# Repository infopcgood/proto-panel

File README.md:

# proto-panel
LED panel PCB project compatible with Sigma Protogen by Coela Can't!

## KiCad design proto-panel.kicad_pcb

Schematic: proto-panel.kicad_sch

Parts:
D1, D2, D3, D4, D5, D6, D7, D8, D9, D10, D11, D12, D13, D14, D15, D16, D17, D18, D19, D20, D21, D22, D23, D24, D25, D26, D27, D28, D29, D30, D31, D32, D33, D34, D35, D36, D37, D38, D39, D40, D41, D42, D43, D44, D45, D46, D47, D48, D49, D50, D51, D52, D53, D54, D55, D56, D57, D58, D59, D60, D61, D62, D63, D64, D65, D66, D67, D68, D69, D70, D71, D72, D73, D74, D75, D76, D77, D78, D79, D80, D81, D82, D83, D84, D85, D86, D87, D88, D89, D90, D91, D92, D93, D94, D95, D96, D97, D98, D99, D100, D101, D102, D103, D104, D105, D106, D107, D108, D109, D110, D111, D112, D113, D114, D115, D116, D117, D118, D119, D120, D121, D122, D123, D124, D125, D126, D127, D128, D129, D130, D131, D132, D133, D134, D135, D136, D137, D138, D139, D140, D141, D142, D143, D144, D145, D146, D147, D148, D149, D150, D151, D152, D153, D154, D155, D156, D157, D158, D159, D160, D161, D162, D163, D164, D165, D166, D167, D168, D169, D170, D171, D172, D173, D174, D175, D176, D177, D178, D179, D180, D181, D182, D183, D184, D185, D186, D187, D188, D189, D190, D191, D192, D193, D194, D195, D196, D197, D198, D199, D200, D201, D202, D203, D204, D205, D206, D207, D208, D209, D210, D211, D212, D213, D214, D215, D216, D217, D218, D219, D220, D221, D222, D223, D224, D225, D226, D227, D228, D229, D230, D231, D232, D233, D234, D235, D236, D237, D238, D239, D240, D241, D242, D243, D244, D245, D246, D247, D248, D249, D250, D251, D252, D253, D254, D255, D256, D257, D258, D259, D260, D261, D262, D263, D264, D265, D266, D267, D268, D269, D270, D271, D272, D273, D274, D275, D276, D277, D278, D279, D280, D281, D282, D283, D284, D285, D286, D287, D288, D289, D290, D291, D292, D293, D294, D295, D296, D297, D298, D299, D300, D301, D302, D303, D304, D305, D306, D307, D308, D309, D310, D311, D312, D313, D314, D315, D316, D317, D318, D319, D320, D321, D322, D323, D324, D325, D326, D327, D328, D329, D330, D331, D332, D333, D334, D335, D336, D337, D338, D339, D340, D341, D342, D343, D344, D345, D346, D347, D348, D349, D350, D351, D352, D353, D354, D355, D356, D357, D358, D359, D360, D361, D362, D363, D364, D365, D366, D367, D368, D369, D370, D371, D372, D373, D374, D375, D376, D377, D378, D379, D380, D381, D382, D383, D384, D385, D386, D387, D388, D389, D390, D391, D392, D393, D394, D395, D396, D397, D398, D399, D400, D401, D402, D403, D404, D405, D406, D407, D408, D409, D410, D411, D412, D413, D414, D415, D416, D417, D418, D419, D420, D421, D422, D423, D424, D425, D426, D427, D428, D429, D430, D431, D432, D433, D434, D435, D436, D437, D438, D439, D440, D441, D442, D443, D444, D445, D446, D447, D448, D449, D450, D451, D452, D453, D454, D455, D456, D457, D458, D459, D460, D461, D462, D463, D464, D465, D466, D467, D468, D469, D470, D471, D472, D473, D474, D475, D476, D477, D478, D479, D480, D481, D482, D483, D484, D485, D486, D487, D488, D489, D490, D491, D492, D493, D494, D495, D496, D497, D498, D499, D500, D501, D502, D503, D504, D505, D506, D507, D508, D509, D510, D511, D512, D513, D514, D515, D516, D517, D518, D519, D520, D521, D522, D523, D524, D525, D526, D527, D528, D529, D530, D531, D532, D533, D534, D535, D536, D537, D538, D539, D540, D541, D542, D543, D544, D545, D546, D547, D548, D549, D550, D551, D552, D553, D554, D555, D556, D557, D558, D559, D560, D561, D562, D563, D564, D565, D566, D567, D568, D569, D570, D571, D572, D573, D574, D575, D576, D577, D578, D579, D580, D581, D582, D583, D584, D585, D586, D587, D588, D589, D590, D591, D592, D593, D594, D595, D596, D597, D598, D599, D600, D601, D602, D603, D604, D605, D606, D607, D608, D609, D610, D611, D612, D613, D614, D615, D616, D617, D618, D619, D620, D621, D622, D623, D624, D625, D626, D627, D628, D629, D630, D631, D632, D633, D634, D635, D636, D637, D638, D639, D640, D641, D642, D643, D644, D645, D646, D647, D648, D649, D650, D651, D652, D653, D654, D655, D656, D657, D658, D659, D660, D661, D662, D663, D664, D665, D666, D667, D668, D669, D670, D671, D672, D673, D674, D675, D676, D677, D678, D679, D680, D681, D682, D683, D684, D685, D686, D687, D688, D689, D690, D691, D692, D693, D694, D695, D696, D697, D698, D699, D700, D701, D702, D703, D704, D705, D706, D707, D708, D709, D710, D711, D712, D713, D714, D715, D716, D717, D718, D719, D720, D721, D722, D723, D724, D725, D726, D727, D728, D729, D730, D731, D733, D734, D735, D736, D737, D738, D739, D740, D741, D742, D743, D744, D745, D746, D747, D748, D749, D750, D751, D752, D753, D754, D755, D756, D757, D758, D759, D760, D761, D762, D763, D764, D765, D766, D767, D768, D769, D770, D771, D772, D773, D774, D775, D776, D778, D779, D780, D781, D782, D783, D784, D785, D786, D787, D788, D789, D790, D791, D792, D793, D794, D795, D796, D797, D798, D799, D800, D801, D802, D803, D804, D805, D806, D807, D808, D809, D810, D811, D812, D813, D814, D815, D816, D817, D818, D819, D820, D822, D823, D824, D825, D826, D827, D828, D829, D830, D831, D832, D833, D834, D835, D836, D837, D838, D839, D840, D841, D842, D843, D844, D845, D846, D847, D848, D849, D850, D851, D852, D853, D854, D855, D856, D857, D858, D859, D860, D861, D862, D864, D865, D866, D867, D868, D869, D870, D871, D872, D873, D874, D875, D876, D877, D878, D879, D880, D881, D882, D883, D884, D885, D886, D887, D888, D889, D890, D891, D892, D893, D894, D895, D896, D897, D898, D899, D900, D901, D902, D903, D904, D905, D906, D907, D908, D909, D910, D911, D912, D913, D914, D915, D916, D917, D918, D919, D920, D921, D922, D923, D924, D925, D926, D927, D928, D929, D930, D931, D932, D933, D934, D935, D936, D937, D938, D939, D940, D941, D942, D943, D944, D945, D946, D947, D948, D949, D950, D951, D952, D953, D954, D955, D956, D957, D958, D959, D960, D961, D962, D963, D964, D965, D966, D967, D968, D969, D970, D971, D972, D973, D974, D975, D976, D977, D978, D979, D980, D981, D982, D983, D984, D985, D986, D987, D988, D989, D990, D991, D992, D993, D994, D995, D996, D997, D998, D999, D1000, D1001, D1002, D1003, D1004, D1005, D1006, D1007, D1008, D1009, D1010, D1011, D1012, D1013, D1014, D1015, D1016, D1017, D1018, D1019, D1020, D1021, D1022, D1023, D1024, D1025, D1026, D1027, D1028, D1029, D1030, D1031, D1032, D1033, D1034, D1035, D1036, D1037, D1038, D1039, D1040, D1041, D1042, D1043, D1044, D1045, D1046, D1047, D1048, D1049, D1050, D1051, D1052, D1053, D1054, D1055, D1056, D1057, D1058, D1059, D1060, D1061, D1062, D1063, D1064, D1065, D1066, D1067, D1068, D1069, D1070, D1071, D1072, D1073, D1074, D1075, D1076, D1077, D1078, D1079, D1080, D1081, D1082, D1083, D1084, D1085, D1086, D1087, D1088, D1089, D1090, D1091, D1092, D1093, D1094, D1095, D1096, D1097, D1098, D1099, D1100, D1101, D1102, D1103, D1104, D1105, D1106, D1107, D1108, D1109, D1110, D1111, D1112, D1113, D1114, D1115, D1116, D1117, D1118, D1119, D1120, D1121, D1122, D1123, D1124, D1125, D1126, D1127, D1128, D1129, D1130, D1131, D1132, D1133, D1134, D1135, D1136, D1137, D1138, D1139, D1140, D1141, D1142, D1143, D1144, D1145, D1146, D1147, D1148, D1149, D1150, D1151, D1152, D1153, D1154, D1155, D1156, D1157, D1158, D1159, D1160, D1161, D1162, D1163, D1164, D1165, D1166, D1167, D1168, D1169, D1170, D1171, D1172, D1173, D1174, D1175, D1176, D1177, D1178, D1179, D1180, D1181, D1182, D1183, D1184, D1185, D1186, D1187, D1188, D1189, D1190, D1191, D1192, D1193, D1194, D1195, D1196, D1197, D1198, D1199, D1200: LED; LED_WS2812B-2020_PLCC4_2.0x2.0mm-VIAPADS; LCSC C965555
D732, D777, D821, D863: LED; LED_WS2812B-2020_PLCC4_2.0x2.0mm-VIAPADS
H1, H2, H3, H4, H5, H6, H7, H8, H9: MountingHole; MountingHole_2.2mm_M2
H10, H11: MountingHole_Pad; MountingHole_2.2mm_M2_Pad
J3: Conn_01x08_Socket; Hirose_FH12-8S-0.5SH_1x08-1MP_P0.50mm_Horizontal

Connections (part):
+5V: D1.4 (VDD), D2.4 (VDD), D3.4 (VDD), D4.4 (VDD), D5.4 (VDD), D6.4 (VDD), D7.4 (VDD), D8.4 (VDD), D9.4 (VDD), D10.4 (VDD), D11.4 (VDD), D12.4 (VDD), D13.4 (VDD), D14.4 (VDD), D15.4 (VDD), D16.4 (VDD), D17.4 (VDD), D18.4 (VDD), D19.4 (VDD), D20.4 (VDD), D21.4 (VDD), D22.4 (VDD), D23.4 (VDD), D24.4 (VDD), D25.4 (VDD), D26.4 (VDD), D27.4 (VDD), D28.4 (VDD), D29.4 (VDD), D30.4 (VDD), D31.4 (VDD), D32.4 (VDD), D33.4 (VDD), D34.4 (VDD), D35.4 (VDD), D36.4 (VDD), D37.4 (VDD), D38.4 (VDD), D39.4 (VDD), D40.4 (VDD), D41.4 (VDD), D42.4 (VDD), D43.4 (VDD), D44.4 (VDD), D45.4 (VDD), D46.4 (VDD), D47.4 (VDD), D48.4 (VDD), D49.4 (VDD), D50.4 (VDD), D51.4 (VDD), D52.4 (VDD), D53.4 (VDD), D54.4 (VDD), D55.4 (VDD), D56.4 (VDD), D57.4 (VDD), D58.4 (VDD), D59.4 (VDD), D60.4 (VDD), D61.4 (VDD), D62.4 (VDD), D63.4 (VDD), D64.4 (VDD), D65.4 (VDD), D66.4 (VDD), D67.4 (VDD), D68.4 (VDD), D69.4 (VDD), D70.4 (VDD), D71.4 (VDD), D72.4 (VDD), D73.4 (VDD), D74.4 (VDD), D75.4 (VDD), D76.4 (VDD), D77.4 (VDD), D78.4 (VDD), D79.4 (VDD), D80.4 (VDD)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
GND: D1.2 (VSS), D2.2 (VSS), D3.2 (VSS), D4.2 (VSS), D5.2 (VSS), D6.2 (VSS), D7.2 (VSS), D8.2 (VSS), D9.2 (VSS), D10.2 (VSS), D11.2 (VSS), D12.2 (VSS), D13.2 (VSS), D14.2 (VSS), D15.2 (VSS), D16.2 (VSS), D17.2 (VSS), D18.2 (VSS), D19.2 (VSS), D20.2 (VSS), D21.2 (VSS), D22.2 (VSS), D23.2 (VSS), D24.2 (VSS), D25.2 (VSS), D26.2 (VSS), D27.2 (VSS), D28.2 (VSS), D29.2 (VSS), D30.2 (VSS), D31.2 (VSS), D32.2 (VSS), D33.2 (VSS), D34.2 (VSS), D35.2 (VSS), D36.2 (VSS), D37.2 (VSS), D38.2 (VSS), D39.2 (VSS), D40.2 (VSS), D41.2 (VSS), D42.2 (VSS), D43.2 (VSS), D44.2 (VSS), D45.2 (VSS), D46.2 (VSS), D47.2 (VSS), D48.2 (VSS), D49.2 (VSS), D50.2 (VSS), D51.2 (VSS), D52.2 (VSS), D53.2 (VSS), D54.2 (VSS), D55.2 (VSS), D56.2 (VSS), D57.2 (VSS), D58.2 (VSS), D59.2 (VSS), D60.2 (VSS), D61.2 (VSS), D62.2 (VSS), D63.2 (VSS), D64.2 (VSS), D65.2 (VSS), D66.2 (VSS), D67.2 (VSS), D68.2 (VSS), D69.2 (VSS), D70.2 (VSS), D71.2 (VSS), D72.2 (VSS), D73.2 (VSS), D74.2 (VSS), D75.2 (VSS), D76.2 (VSS), D77.2 (VSS), D78.2 (VSS), D79.2 (VSS), D80.2 (VSS)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
unnamed: D1.1 (DOUT), D2.3 (DIN)
unnamed: D2.1 (DOUT), D3.3 (DIN)
unnamed: D3.1 (DOUT), D4.3 (DIN)
unnamed: D4.1 (DOUT), D5.3 (DIN)
unnamed: D5.1 (DOUT), D6.3 (DIN)
unnamed: D6.1 (DOUT), D7.3 (DIN)
unnamed: D7.1 (DOUT), D8.3 (DIN)
unnamed: D8.1 (DOUT), D9.3 (DIN)
unnamed: D9.1 (DOUT), D10.3 (DIN)
unnamed: D10.1 (DOUT), D11.3 (DIN)
unnamed: D11.1 (DOUT), D12.3 (DIN)
unnamed: D12.1 (DOUT), D13.3 (DIN)
unnamed: D13.1 (DOUT), D14.3 (DIN)
unnamed: D14.1 (DOUT), D15.3 (DIN)
unnamed: D15.1 (DOUT), D16.3 (DIN)
unnamed: D16.1 (DOUT), D17.3 (DIN)
unnamed: D17.1 (DOUT), D18.3 (DIN)
unnamed: D18.1 (DOUT), D19.3 (DIN)
unnamed: D19.1 (DOUT), D20.3 (DIN)
unnamed: D20.1 (DOUT), D21.3 (DIN)
unnamed: D21.1 (DOUT), D22.3 (DIN)
unnamed: D22.1 (DOUT), D23.3 (DIN)
unnamed: D23.1 (DOUT), D24.3 (DIN)
unnamed: D24.1 (DOUT), D25.3 (DIN)
unnamed: D25.1 (DOUT), D26.3 (DIN)
unnamed: D26.1 (DOUT), D27.3 (DIN)
unnamed: D27.1 (DOUT), D28.3 (DIN)
unnamed: D28.1 (DOUT), D29.3 (DIN)
unnamed: D29.1 (DOUT), D30.3 (DIN)
unnamed: D30.1 (DOUT), D31.3 (DIN)
unnamed: D31.1 (DOUT), D32.3 (DIN)
unnamed: D32.1 (DOUT), D33.3 (DIN)
unnamed: D33.1 (DOUT), D34.3 (DIN)
unnamed: D34.1 (DOUT), D35.3 (DIN)
unnamed: D35.1 (DOUT), D36.3 (DIN)
unnamed: D36.1 (DOUT), D37.3 (DIN)
unnamed: D37.1 (DOUT), D38.3 (DIN)
unnamed: D38.1 (DOUT), D39.3 (DIN)
unnamed: D39.1 (DOUT), D40.3 (DIN)
unnamed: D40.1 (DOUT), D41.3 (DIN)
unnamed: D41.1 (DOUT), D42.3 (DIN)
unnamed: D42.1 (DOUT), D43.3 (DIN)
unnamed: D43.1 (DOUT), D44.3 (DIN)
unnamed: D44.1 (DOUT), D45.3 (DIN)
unnamed: D45.1 (DOUT), D46.3 (DIN)
unnamed: D46.1 (DOUT), D47.3 (DIN)
unnamed: D47.1 (DOUT), D48.3 (DIN)
unnamed: D48.1 (DOUT), D49.3 (DIN)
unnamed: D49.1 (DOUT), D50.3 (DIN)
unnamed: D50.1 (DOUT), D51.3 (DIN)
unnamed: D51.1 (DOUT), D52.3 (DIN)
unnamed: D52.1 (DOUT), D53.3 (DIN)
unnamed: D53.1 (DOUT), D54.3 (DIN)
unnamed: D54.1 (DOUT), D55.3 (DIN)
unnamed: D55.1 (DOUT), D56.3 (DIN)
unnamed: D56.1 (DOUT), D57.3 (DIN)
unnamed: D57.1 (DOUT), D58.3 (DIN)
unnamed: D58.1 (DOUT), D59.3 (DIN)
unnamed: D59.1 (DOUT), D60.3 (DIN)
unnamed: D60.1 (DOUT), D61.3 (DIN)
unnamed: D61.1 (DOUT), D62.3 (DIN)
unnamed: D62.1 (DOUT), D63.3 (DIN)
unnamed: D63.1 (DOUT), D64.3 (DIN)
unnamed: D64.1 (DOUT), D65.3 (DIN)
unnamed: D65.1 (DOUT), D66.3 (DIN)
unnamed: D66.1 (DOUT), D67.3 (DIN)
unnamed: D67.1 (DOUT), D68.3 (DIN)
unnamed: D68.1 (DOUT), D69.3 (DIN)
unnamed: D69.1 (DOUT), D70.3 (DIN)
unnamed: D70.1 (DOUT), D71.3 (DIN)
unnamed: D71.1 (DOUT), D72.3 (DIN)
unnamed: D72.1 (DOUT), D73.3 (DIN)
unnamed: D73.1 (DOUT), D74.3 (DIN)
unnamed: D74.1 (DOUT), D75.3 (DIN)
unnamed: D75.1 (DOUT), D76.3 (DIN)
unnamed: D76.1 (DOUT), D77.3 (DIN)
unnamed: D77.1 (DOUT), D78.3 (DIN)
unnamed: D78.1 (DOUT), D79.3 (DIN)
unnamed: D79.1 (DOUT), D80.3 (DIN)
unnamed: D80.1 (DOUT), D81.3 (DIN)
unnamed: D81.1 (DOUT), D82.3 (DIN)
unnamed: D82.1 (DOUT), D83.3 (DIN)
unnamed: D83.1 (DOUT), D84.3 (DIN)
unnamed: D84.1 (DOUT), D85.3 (DIN)
unnamed: D85.1 (DOUT), D86.3 (DIN)
unnamed: D86.1 (DOUT), D87.3 (DIN)
unnamed: D87.1 (DOUT), D88.3 (DIN)
unnamed: D88.1 (DOUT), D89.3 (DIN)
unnamed: D89.1 (DOUT), D90.3 (DIN)
unnamed: D90.1 (DOUT), D91.3 (DIN)
unnamed: D91.1 (DOUT), D92.3 (DIN)
unnamed: D92.1 (DOUT), D93.3 (DIN)
unnamed: D93.1 (DOUT), D94.3 (DIN)
unnamed: D94.1 (DOUT), D95.3 (DIN)
unnamed: D95.1 (DOUT), D96.3 (DIN)
unnamed: D96.1 (DOUT), D97.3 (DIN)
unnamed: D97.1 (DOUT), D98.3 (DIN)
unnamed: D98.1 (DOUT), D99.3 (DIN)
unnamed: D99.1 (DOUT), D100.3 (DIN)
unnamed: D100.1 (DOUT), D101.3 (DIN)
unnamed: D101.1 (DOUT), D102.3 (DIN)
unnamed: D102.1 (DOUT), D103.3 (DIN)
unnamed: D103.1 (DOUT), D104.3 (DIN)
unnamed: D104.1 (DOUT), D105.3 (DIN)
unnamed: D105.1 (DOUT), D106.3 (DIN)
unnamed: D106.1 (DOUT), D107.3 (DIN)
unnamed: D107.1 (DOUT), D108.3 (DIN)
unnamed: D108.1 (DOUT), D109.3 (DIN)
unnamed: D109.1 (DOUT), D110.3 (DIN)
unnamed: D110.1 (DOUT), D111.3 (DIN)
unnamed: D111.1 (DOUT), D112.3 (DIN)
unnamed: D112.1 (DOUT), D113.3 (DIN)
unnamed: D113.1 (DOUT), D114.3 (DIN)
unnamed: D114.1 (DOUT), D115.3 (DIN)
unnamed: D115.1 (DOUT), D116.3 (DIN)
unnamed: D116.1 (DOUT), D117.3 (DIN)
unnamed: D117.1 (DOUT), D118.3 (DIN)
unnamed: D118.1 (DOUT), D119.3 (DIN)
unnamed: D119.1 (DOUT), D120.3 (DIN)
unnamed: D120.1 (DOUT), D121.3 (DIN)
unnamed: D121.1 (DOUT), D122.3 (DIN)
unnamed: D122.1 (DOUT), D123.3 (DIN)
unnamed: D123.1 (DOUT), D124.3 (DIN)
unnamed: D124.1 (DOUT), D125.3 (DIN)
unnamed: D125.1 (DOUT), D126.3 (DIN)
unnamed: D126.1 (DOUT), D127.3 (DIN)
unnamed: D127.1 (DOUT), D128.3 (DIN)
unnamed: D128.1 (DOUT), D129.3 (DIN)
unnamed: D129.1 (DOUT), D130.3 (DIN)
unnamed: D130.1 (DOUT), D131.3 (DIN)
unnamed: D131.1 (DOUT), D132.3 (DIN)
unnamed: D132.1 (DOUT), D133.3 (DIN)
unnamed: D133.1 (DOUT), D134.3 (DIN)
unnamed: D134.1 (DOUT), D135.3 (DIN)
unnamed: D135.1 (DOUT), D136.3 (DIN)
unnamed: D136.1 (DOUT), D137.3 (DIN)
unnamed: D137.1 (DOUT), D138.3 (DIN)
unnamed: D138.1 (DOUT), D139.3 (DIN)
unnamed: D139.1 (DOUT), D140.3 (DIN)
unnamed: D140.1 (DOUT), D141.3 (DIN)
unnamed: D141.1 (DOUT), D142.3 (DIN)
unnamed: D142.1 (DOUT), D143.3 (DIN)
unnamed: D143.1 (DOUT), D144.3 (DIN)
unnamed: D144.1 (DOUT), D145.3 (DIN)
unnamed: D145.1 (DOUT), D146.3 (DIN)
unnamed: D146.1 (DOUT), D147.3 (DIN)
unnamed: D147.1 (DOUT), D148.3 (DIN)
unnamed: D148.1 (DOUT), D149.3 (DIN)
unnamed: D149.1 (DOUT), D150.3 (DIN)
unnamed: D151.1 (DOUT), D152.3 (DIN)
unnamed: D152.1 (DOUT), D153.3 (DIN)
unnamed: D153.1 (DOUT), D154.3 (DIN)
unnamed: D154.1 (DOUT), D155.3 (DIN)
unnamed: D155.1 (DOUT), D156.3 (DIN)
unnamed: D156.1 (DOUT), D157.3 (DIN)
unnamed: D157.1 (DOUT), D158.3 (DIN)
unnamed: D158.1 (DOUT), D159.3 (DIN)
unnamed: D159.1 (DOUT), D160.3 (DIN)
unnamed: D160.1 (DOUT), D161.3 (DIN)
unnamed: D161.1 (DOUT), D162.3 (DIN)
unnamed: D162.1 (DOUT), D163.3 (DIN)
unnamed: D163.1 (DOUT), D164.3 (DIN)
unnamed: D164.1 (DOUT), D165.3 (DIN)
unnamed: D165.1 (DOUT), D166.3 (DIN)
unnamed: D166.1 (DOUT), D167.3 (DIN)
unnamed: D167.1 (DOUT), D168.3 (DIN)
unnamed: D168.1 (DOUT), D169.3 (DIN)
unnamed: D169.1 (DOUT), D170.3 (DIN)
unnamed: D170.1 (DOUT), D171.3 (DIN)
unnamed: D171.1 (DOUT), D172.3 (DIN)
unnamed: D172.1 (DOUT), D173.3 (DIN)
unnamed: D173.1 (DOUT), D174.3 (DIN)
unnamed: D174.1 (DOUT), D175.3 (DIN)
unnamed: D175.1 (DOUT), D176.3 (DIN)
unnamed: D176.1 (DOUT), D177.3 (DIN)
unnamed: D177.1 (DOUT), D178.3 (DIN)
unnamed: D178.1 (DOUT), D179.3 (DIN)
unnamed: D179.1 (DOUT), D180.3 (DIN)
unnamed: D180.1 (DOUT), D181.3 (DIN)
unnamed: D181.1 (DOUT), D182.3 (DIN)
unnamed: D182.1 (DOUT), D183.3 (DIN)
unnamed: D183.1 (DOUT), D184.3 (DIN)
unnamed: D184.1 (DOUT), D185.3 (DIN)
unnamed: D185.1 (DOUT), D186.3 (DIN)
unnamed: D186.1 (DOUT), D187.3 (DIN)
unnamed: D187.1 (DOUT), D188.3 (DIN)
unnamed: D188.1 (DOUT), D189.3 (DIN)
unnamed: D189.1 (DOUT), D190.3 (DIN)
unnamed: D190.1 (DOUT), D191.3 (DIN)
unnamed: D191.1 (DOUT), D192.3 (DIN)
unnamed: D192.1 (DOUT), D193.3 (DIN)
unnamed: D193.1 (DOUT), D194.3 (DIN)
unnamed: D194.1 (DOUT), D195.3 (DIN)
unnamed: D195.1 (DOUT), D196.3 (DIN)
unnamed: D196.1 (DOUT), D197.3 (DIN)
unnamed: D197.1 (DOUT), D198.3 (DIN)
unnamed: D198.1 (DOUT), D199.3 (DIN)
unnamed: D199.1 (DOUT), D200.3 (DIN)
unnamed: D200.1 (DOUT), D201.3 (DIN)
unnamed: D201.1 (DOUT), D202.3 (DIN)
unnamed: D202.1 (DOUT), D203.3 (DIN)
unnamed: D203.1 (DOUT), D204.3 (DIN)
unnamed: D204.1 (DOUT), D205.3 (DIN)
unnamed: D205.1 (DOUT), D206.3 (DIN)
unnamed: D206.1 (DOUT), D207.3 (DIN)
unnamed: D207.1 (DOUT), D208.3 (DIN)
unnamed: D208.1 (DOUT), D209.3 (DIN)
unnamed: D209.1 (DOUT), D210.3 (DIN)
unnamed: D210.1 (DOUT), D211.3 (DIN)
unnamed: D211.1 (DOUT), D212.3 (DIN)
unnamed: D212.1 (DOUT), D213.3 (DIN)
unnamed: D213.1 (DOUT), D214.3 (DIN)
unnamed: D214.1 (DOUT), D215.3 (DIN)
unnamed: D215.1 (DOUT), D216.3 (DIN)
unnamed: D216.1 (DOUT), D217.3 (DIN)
unnamed: D217.1 (DOUT), D218.3 (DIN)
unnamed: D218.1 (DOUT), D219.3 (DIN)
unnamed: D219.1 (DOUT), D220.3 (DIN)
unnamed: D220.1 (DOUT), D221.3 (DIN)
unnamed: D221.1 (DOUT), D222.3 (DIN)
unnamed: D222.1 (DOUT), D223.3 (DIN)
unnamed: D223.1 (DOUT), D224.3 (DIN)
unnamed: D224.1 (DOUT), D225.3 (DIN)
unnamed: D225.1 (DOUT), D226.3 (DIN)
unnamed: D226.1 (DOUT), D227.3 (DIN)
unnamed: D227.1 (DOUT), D228.3 (DIN)
unnamed: D228.1 (DOUT), D229.3 (DIN)
unnamed: D229.1 (DOUT), D230.3 (DIN)
unnamed: D230.1 (DOUT), D231.3 (DIN)
unnamed: D231.1 (DOUT), D232.3 (DIN)
unnamed: D232.1 (DOUT), D233.3 (DIN)
unnamed: D233.1 (DOUT), D234.3 (DIN)
unnamed: D234.1 (DOUT), D235.3 (DIN)
unnamed: D235.1 (DOUT), D236.3 (DIN)
unnamed: D236.1 (DOUT), D237.3 (DIN)
unnamed: D237.1 (DOUT), D238.3 (DIN)
unnamed: D238.1 (DOUT), D239.3 (DIN)
unnamed: D239.1 (DOUT), D240.3 (DIN)
unnamed: D240.1 (DOUT), D241.3 (DIN)
unnamed: D241.1 (DOUT), D242.3 (DIN)
unnamed: D242.1 (DOUT), D243.3 (DIN)
unnamed: D243.1 (DOUT), D244.3 (DIN)
unnamed: D244.1 (DOUT), D245.3 (DIN)
unnamed: D245.1 (DOUT), D246.3 (DIN)
unnamed: D246.1 (DOUT), D247.3 (DIN)
unnamed: D247.1 (DOUT), D248.3 (DIN)
unnamed: D248.1 (DOUT), D249.3 (DIN)
unnamed: D249.1 (DOUT), D250.3 (DIN)
unnamed: D250.1 (DOUT), D251.3 (DIN)
unnamed: D251.1 (DOUT), D252.3 (DIN)
unnamed: D252.1 (DOUT), D253.3 (DIN)
unnamed: D253.1 (DOUT), D254.3 (DIN)
unnamed: D254.1 (DOUT), D255.3 (DIN)
unnamed: D255.1 (DOUT), D256.3 (DIN)
unnamed: D256.1 (DOUT), D257.3 (DIN)
unnamed: D257.1 (DOUT), D258.3 (DIN)
unnamed: D258.1 (DOUT), D259.3 (DIN)
unnamed: D259.1 (DOUT), D260.3 (DIN)
unnamed: D260.1 (DOUT), D261.3 (DIN)
unnamed: D261.1 (DOUT), D262.3 (DIN)
unnamed: D262.1 (DOUT), D263.3 (DIN)
unnamed: D263.1 (DOUT), D264.3 (DIN)
unnamed: D264.1 (DOUT), D265.3 (DIN)
unnamed: D265.1 (DOUT), D266.3 (DIN)
unnamed: D266.1 (DOUT), D267.3 (DIN)
unnamed: D267.1 (DOUT), D268.3 (DIN)
unnamed: D268.1 (DOUT), D269.3 (DIN)
unnamed: D269.1 (DOUT), D270.3 (DIN)
unnamed: D270.1 (DOUT), D271.3 (DIN)
unnamed: D271.1 (DOUT), D272.3 (DIN)
unnamed: D272.1 (DOUT), D273.3 (DIN)
unnamed: D273.1 (DOUT), D274.3 (DIN)
unnamed: D274.1 (DOUT), D275.3 (DIN)
unnamed: D275.1 (DOUT), D276.3 (DIN)
unnamed: D276.1 (DOUT), D277.3 (DIN)
unnamed: D277.1 (DOUT), D278.3 (DIN)
unnamed: D278.1 (DOUT), D279.3 (DIN)
unnamed: D279.1 (DOUT), D280.3 (DIN)
unnamed: D280.1 (DOUT), D281.3 (DIN)
unnamed: D281.1 (DOUT), D282.3 (DIN)
unnamed: D282.1 (DOUT), D283.3 (DIN)
unnamed: D283.1 (DOUT), D284.3 (DIN)
unnamed: D284.1 (DOUT), D285.3 (DIN)
unnamed: D285.1 (DOUT), D286.3 (DIN)
unnamed: D286.1 (DOUT), D287.3 (DIN)
unnamed: D287.1 (DOUT), D288.3 (DIN)
unnamed: D288.1 (DOUT), D289.3 (DIN)
unnamed: D289.1 (DOUT), D290.3 (DIN)
unnamed: D290.1 (DOUT), D291.3 (DIN)
unnamed: D291.1 (DOUT), D292.3 (DIN)
unnamed: D292.1 (DOUT), D293.3 (DIN)
unnamed: D293.1 (DOUT), D294.3 (DIN)
unnamed: D294.1 (DOUT), D295.3 (DIN)
unnamed: D295.1 (DOUT), D296.3 (DIN)
unnamed: D296.1 (DOUT), D297.3 (DIN)
unnamed: D297.1 (DOUT), D298.3 (DIN)
unnamed: D298.1 (DOUT), D299.3 (DIN)
unnamed: D299.1 (DOUT), D300.3 (DIN)
unnamed: D301.1 (DOUT), D302.3 (DIN)
unnamed: D302.1 (DOUT), D303.3 (DIN)
unnamed: D303.1 (DOUT), D304.3 (DIN)
unnamed: D304.1 (DOUT), D305.3 (DIN)
unnamed: D305.1 (DOUT), D306.3 (DIN)
unnamed: D306.1 (DOUT), D307.3 (DIN)
unnamed: D307.1 (DOUT), D308.3 (DIN)
unnamed: D308.1 (DOUT), D309.3 (DIN)
unnamed: D309.1 (DOUT), D310.3 (DIN)
unnamed: D310.1 (DOUT), D311.3 (DIN)
unnamed: D311.1 (DOUT), D312.3 (DIN)
unnamed: D312.1 (DOUT), D313.3 (DIN)
unnamed: D313.1 (DOUT), D314.3 (DIN)
unnamed: D314.1 (DOUT), D315.3 (DIN)
unnamed: D315.1 (DOUT), D316.3 (DIN)
unnamed: D316.1 (DOUT), D317.3 (DIN)
unnamed: D317.1 (DOUT), D318.3 (DIN)
unnamed: D318.1 (DOUT), D319.3 (DIN)
unnamed: D319.1 (DOUT), D320.3 (DIN)
unnamed: D320.1 (DOUT), D321.3 (DIN)
unnamed: D321.1 (DOUT), D322.3 (DIN)
unnamed: D322.1 (DOUT), D323.3 (DIN)
unnamed: D323.1 (DOUT), D324.3 (DIN)
unnamed: D324.1 (DOUT), D325.3 (DIN)
unnamed: D325.1 (DOUT), D326.3 (DIN)
unnamed: D326.1 (DOUT), D327.3 (DIN)
unnamed: D327.1 (DOUT), D328.3 (DIN)
unnamed: D328.1 (DOUT), D329.3 (DIN)
unnamed: D329.1 (DOUT), D330.3 (DIN)
unnamed: D330.1 (DOUT), D331.3 (DIN)
unnamed: D331.1 (DOUT), D332.3 (DIN)
unnamed: D332.1 (DOUT), D333.3 (DIN)
unnamed: D333.1 (DOUT), D334.3 (DIN)
unnamed: D334.1 (DOUT), D335.3 (DIN)
unnamed: D335.1 (DOUT), D336.3 (DIN)
unnamed: D336.1 (DOUT), D337.3 (DIN)
unnamed: D337.1 (DOUT), D338.3 (DIN)
unnamed: D338.1 (DOUT), D339.3 (DIN)
unnamed: D339.1 (DOUT), D340.3 (DIN)
unnamed: D340.1 (DOUT), D341.3 (DIN)
unnamed: D341.1 (DOUT), D342.3 (DIN)
unnamed: D342.1 (DOUT), D343.3 (DIN)
unnamed: D343.1 (DOUT), D344.3 (DIN)
unnamed: D344.1 (DOUT), D345.3 (DIN)
unnamed: D345.1 (DOUT), D346.3 (DIN)
unnamed: D346.1 (DOUT), D347.3 (DIN)
unnamed: D347.1 (DOUT), D348.3 (DIN)
unnamed: D348.1 (DOUT), D349.3 (DIN)
unnamed: D349.1 (DOUT), D350.3 (DIN)
unnamed: D350.1 (DOUT), D351.3 (DIN)
unnamed: D351.1 (DOUT), D352.3 (DIN)
unnamed: D352.1 (DOUT), D353.3 (DIN)
unnamed: D353.1 (DOUT), D354.3 (DIN)
unnamed: D354.1 (DOUT), D355.3 (DIN)
unnamed: D355.1 (DOUT), D356.3 (DIN)
unnamed: D356.1 (DOUT), D357.3 (DIN)
unnamed: D357.1 (DOUT), D358.3 (DIN)
unnamed: D358.1 (DOUT), D359.3 (DIN)
unnamed: D359.1 (DOUT), D360.3 (DIN)
unnamed: D360.1 (DOUT), D361.3 (DIN)
unnamed: D361.1 (DOUT), D362.3 (DIN)
unnamed: D362.1 (DOUT), D363.3 (DIN)
unnamed: D363.1 (DOUT), D364.3 (DIN)
unnamed: D364.1 (DOUT), D365.3 (DIN)
unnamed: D365.1 (DOUT), D366.3 (DIN)
unnamed: D366.1 (DOUT), D367.3 (DIN)
unnamed: D367.1 (DOUT), D368.3 (DIN)
unnamed: D368.1 (DOUT), D369.3 (DIN)
unnamed: D369.1 (DOUT), D370.3 (DIN)
unnamed: D370.1 (DOUT), D371.3 (DIN)
unnamed: D371.1 (DOUT), D372.3 (DIN)
unnamed: D372.1 (DOUT), D373.3 (DIN)
unnamed: D373.1 (DOUT), D374.3 (DIN)
unnamed: D374.1 (DOUT), D375.3 (DIN)
unnamed: D375.1 (DOUT), D376.3 (DIN)
unnamed: D376.1 (DOUT), D377.3 (DIN)
unnamed: D377.1 (DOUT), D378.3 (DIN)
unnamed: D378.1 (DOUT), D379.3 (DIN)
unnamed: D379.1 (DOUT), D380.3 (DIN)
unnamed: D380.1 (DOUT), D381.3 (DIN)
unnamed: D381.1 (DOUT), D382.3 (DIN)
unnamed: D382.1 (DOUT), D383.3 (DIN)
unnamed: D383.1 (DOUT), D384.3 (DIN)
unnamed: D384.1 (DOUT), D385.3 (DIN)
unnamed: D385.1 (DOUT), D386.3 (DIN)
unnamed: D386.1 (DOUT), D387.3 (DIN)
unnamed: D387.1 (DOUT), D388.3 (DIN)
unnamed: D388.1 (DOUT), D389.3 (DIN)
unnamed: D389.1 (DOUT), D390.3 (DIN)
unnamed: D390.1 (DOUT), D391.3 (DIN)
unnamed: D391.1 (DOUT), D392.3 (DIN)
unnamed: D392.1 (DOUT), D393.3 (DIN)
unnamed: D393.1 (DOUT), D394.3 (DIN)
unnamed: D394.1 (DOUT), D395.3 (DIN)
unnamed: D395.1 (DOUT), D396.3 (DIN)
unnamed: D396.1 (DOUT), D397.3 (DIN)
unnamed: D397.1 (DOUT), D398.3 (DIN)
unnamed: D398.1 (DOUT), D399.3 (DIN)
unnamed: D399.1 (DOUT), D400.3 (DIN)
unnamed: D400.1 (DOUT), D401.3 (DIN)
unnamed: D401.1 (DOUT), D402.3 (DIN)
unnamed: D402.1 (DOUT), D403.3 (DIN)
unnamed: D403.1 (DOUT), D404.3 (DIN)
unnamed: D404.1 (DOUT), D405.3 (DIN)
unnamed: D405.1 (DOUT), D406.3 (DIN)
unnamed: D406.1 (DOUT), D407.3 (DIN)
unnamed: D407.1 (DOUT), D408.3 (DIN)
unnamed: D408.1 (DOUT), D409.3 (DIN)
unnamed: D409.1 (DOUT), D410.3 (DIN)
unnamed: D410.1 (DOUT), D411.3 (DIN)
unnamed: D411.1 (DOUT), D412.3 (DIN)
unnamed: D412.1 (DOUT), D413.3 (DIN)
unnamed: D413.1 (DOUT), D414.3 (DIN)
unnamed: D414.1 (DOUT), D415.3 (DIN)
unnamed: D415.1 (DOUT), D416.3 (DIN)
unnamed: D416.1 (DOUT), D417.3 (DIN)
unnamed: D417.1 (DOUT), D418.3 (DIN)
unnamed: D418.1 (DOUT), D419.3 (DIN)
unnamed: D419.1 (DOUT), D420.3 (DIN)
unnamed: D420.1 (DOUT), D421.3 (DIN)
unnamed: D421.1 (DOUT), D422.3 (DIN)
unnamed: D422.1 (DOUT), D423.3 (DIN)
unnamed: D423.1 (DOUT), D424.3 (DIN)
unnamed: D424.1 (DOUT), D425.3 (DIN)
unnamed: D425.1 (DOUT), D426.3 (DIN)
unnamed: D426.1 (DOUT), D427.3 (DIN)
unnamed: D427.1 (DOUT), D428.3 (DIN)
unnamed: D428.1 (DOUT), D429.3 (DIN)
unnamed: D429.1 (DOUT), D430.3 (DIN)
unnamed: D430.1 (DOUT), D431.3 (DIN)
unnamed: D431.1 (DOUT), D432.3 (DIN)
unnamed: D432.1 (DOUT), D433.3 (DIN)
unnamed: D433.1 (DOUT), D434.3 (DIN)
unnamed: D434.1 (DOUT), D435.3 (DIN)
unnamed: D435.1 (DOUT), D436.3 (DIN)
unnamed: D436.1 (DOUT), D437.3 (DIN)
unnamed: D437.1 (DOUT), D438.3 (DIN)
unnamed: D438.1 (DOUT), D439.3 (DIN)
unnamed: D439.1 (DOUT), D440.3 (DIN)
unnamed: D440.1 (DOUT), D441.3 (DIN)
unnamed: D441.1 (DOUT), D442.3 (DIN)
unnamed: D442.1 (DOUT), D443.3 (DIN)
unnamed: D443.1 (DOUT), D444.3 (DIN)
unnamed: D444.1 (DOUT), D445.3 (DIN)
unnamed: D445.1 (DOUT), D446.3 (DIN)
unnamed: D446.1 (DOUT), D447.3 (DIN)
unnamed: D447.1 (DOUT), D448.3 (DIN)
unnamed: D448.1 (DOUT), D449.3 (DIN)
unnamed: D449.1 (DOUT), D450.3 (DIN)
unnamed: D451.1 (DOUT), D452.3 (DIN)
unnamed: D452.1 (DOUT), D453.3 (DIN)
unnamed: D453.1 (DOUT), D454.3 (DIN)
unnamed: D454.1 (DOUT), D455.3 (DIN)
unnamed: D455.1 (DOUT), D456.3 (DIN)
unnamed: D456.1 (DOUT), D457.3 (DIN)
unnamed: D457.1 (DOUT), D458.3 (DIN)
unnamed: D458.1 (DOUT), D459.3 (DIN)
unnamed: D459.1 (DOUT), D460.3 (DIN)
unnamed: D460.1 (DOUT), D461.3 (DIN)
unnamed: D461.1 (DOUT), D462.3 (DIN)
unnamed: D462.1 (DOUT), D463.3 (DIN)
unnamed: D463.1 (DOUT), D464.3 (DIN)
unnamed: D464.1 (DOUT), D465.3 (DIN)
unnamed: D465.1 (DOUT), D466.3 (DIN)
unnamed: D466.1 (DOUT), D467.3 (DIN)
unnamed: D467.1 (DOUT), D468.3 (DIN)
unnamed: D468.1 (DOUT), D469.3 (DIN)
unnamed: D469.1 (DOUT), D470.3 (DIN)
unnamed: D470.1 (DOUT), D471.3 (DIN)
unnamed: D471.1 (DOUT), D472.3 (DIN)
unnamed: D472.1 (DOUT), D473.3 (DIN)
unnamed: D473.1 (DOUT), D474.3 (DIN)
unnamed: D474.1 (DOUT), D475.3 (DIN)
unnamed: D475.1 (DOUT), D476.3 (DIN)
unnamed: D476.1 (DOUT), D477.3 (DIN)
unnamed: D477.1 (DOUT), D478.3 (DIN)
unnamed: D478.1 (DOUT), D479.3 (DIN)
unnamed: D479.1 (DOUT), D480.3 (DIN)
unnamed: D480.1 (DOUT), D481.3 (DIN)
unnamed: D481.1 (DOUT), D482.3 (DIN)
unnamed: D482.1 (DOUT), D483.3 (DIN)
unnamed: D483.1 (DOUT), D484.3 (DIN)
unnamed: D484.1 (DOUT), D485.3 (DIN)
unnamed: D485.1 (DOUT), D486.3 (DIN)
unnamed: D486.1 (DOUT), D487.3 (DIN)
unnamed: D487.1 (DOUT), D488.3 (DIN)
unnamed: D488.1 (DOUT), D489.3 (DIN)
unnamed: D489.1 (DOUT), D490.3 (DIN)
unnamed: D490.1 (DOUT), D491.3 (DIN)
unnamed: D491.1 (DOUT), D492.3 (DIN)
unnamed: D492.1 (DOUT), D493.3 (DIN)
unnamed: D493.1 (DOUT), D494.3 (DIN)
unnamed: D494.1 (DOUT), D495.3 (DIN)
unnamed: D495.1 (DOUT), D496.3 (DIN)
unnamed: D496.1 (DOUT), D497.3 (DIN)
unnamed: D497.1 (DOUT), D498.3 (DIN)
unnamed: D498.1 (DOUT), D499.3 (DIN)
unnamed: D499.1 (DOUT), D500.3 (DIN)
unnamed: D500.1 (DOUT), D501.3 (DIN)
unnamed: D501.1 (DOUT), D502.3 (DIN)
unnamed: D502.1 (DOUT), D503.3 (DIN)
unnamed: D503.1 (DOUT), D504.3 (DIN)
unnamed: D504.1 (DOUT), D505.3 (DIN)
unnamed: D505.1 (DOUT), D506.3 (DIN)
unnamed: D506.1 (DOUT), D507.3 (DIN)
unnamed: D507.1 (DOUT), D508.3 (DIN)
unnamed: D508.1 (DOUT), D509.3 (DIN)
unnamed: D509.1 (DOUT), D510.3 (DIN)
unnamed: D510.1 (DOUT), D511.3 (DIN)
unnamed: D511.1 (DOUT), D512.3 (DIN)
unnamed: D512.1 (DOUT), D513.3 (DIN)
unnamed: D513.1 (DOUT), D514.3 (DIN)
unnamed: D514.1 (DOUT), D515.3 (DIN)
unnamed: D515.1 (DOUT), D516.3 (DIN)
unnamed: D516.1 (DOUT), D517.3 (DIN)
unnamed: D517.1 (DOUT), D518.3 (DIN)
unnamed: D518.1 (DOUT), D519.3 (DIN)
unnamed: D519.1 (DOUT), D520.3 (DIN)
unnamed: D520.1 (DOUT), D521.3 (DIN)
unnamed: D521.1 (DOUT), D522.3 (DIN)
unnamed: D522.1 (DOUT), D523.3 (DIN)
unnamed: D523.1 (DOUT), D524.3 (DIN)
unnamed: D524.1 (DOUT), D525.3 (DIN)
unnamed: D525.1 (DOUT), D526.3 (DIN)
unnamed: D526.1 (DOUT), D527.3 (DIN)
unnamed: D527.1 (DOUT), D528.3 (DIN)
unnamed: D528.1 (DOUT), D529.3 (DIN)
unnamed: D529.1 (DOUT), D530.3 (DIN)
unnamed: D530.1 (DOUT), D531.3 (DIN)
unnamed: D531.1 (DOUT), D532.3 (DIN)
unnamed: D532.1 (DOUT), D533.3 (DIN)
unnamed: D533.1 (DOUT), D534.3 (DIN)
unnamed: D534.1 (DOUT), D535.3 (DIN)
unnamed: D535.1 (DOUT), D536.3 (DIN)
unnamed: D536.1 (DOUT), D537.3 (DIN)
unnamed: D537.1 (DOUT), D538.3 (DIN)
unnamed: D538.1 (DOUT), D539.3 (DIN)
unnamed: D539.1 (DOUT), D540.3 (DIN)
unnamed: D540.1 (DOUT), D541.3 (DIN)
unnamed: D541.1 (DOUT), D542.3 (DIN)
unnamed: D542.1 (DOUT), D543.3 (DIN)
unnamed: D543.1 (DOUT), D544.3 (DIN)
unnamed: D544.1 (DOUT), D545.3 (DIN)
unnamed: D545.1 (DOUT), D546.3 (DIN)
unnamed: D546.1 (DOUT), D547.3 (DIN)
unnamed: D547.1 (DOUT), D548.3 (DIN)
unnamed: D548.1 (DOUT), D549.3 (DIN)
unnamed: D549.1 (DOUT), D550.3 (DIN)
unnamed: D550.1 (DOUT), D551.3 (DIN)
unnamed: D551.1 (DOUT), D552.3 (DIN)
unnamed: D552.1 (DOUT), D553.3 (DIN)
unnamed: D553.1 (DOUT), D554.3 (DIN)
unnamed: D554.1 (DOUT), D555.3 (DIN)
unnamed: D555.1 (DOUT), D556.3 (DIN)
unnamed: D556.1 (DOUT), D557.3 (DIN)
unnamed: D557.1 (DOUT), D558.3 (DIN)
unnamed: D558.1 (DOUT), D559.3 (DIN)
unnamed: D559.1 (DOUT), D560.3 (DIN)
unnamed: D560.1 (DOUT), D561.3 (DIN)
unnamed: D561.1 (DOUT), D562.3 (DIN)
unnamed: D562.1 (DOUT), D563.3 (DIN)
unnamed: D563.1 (DOUT), D564.3 (DIN)
unnamed: D564.1 (DOUT), D565.3 (DIN)
unnamed: D565.1 (DOUT), D566.3 (DIN)
unnamed: D566.1 (DOUT), D567.3 (DIN)
unnamed: D567.1 (DOUT), D568.3 (DIN)
unnamed: D568.1 (DOUT), D569.3 (DIN)
unnamed: D569.1 (DOUT), D570.3 (DIN)
unnamed: D570.1 (DOUT), D571.3 (DIN)
unnamed: D571.1 (DOUT), D572.3 (DIN)
unnamed: D572.1 (DOUT), D573.3 (DIN)
unnamed: D573.1 (DOUT), D574.3 (DIN)
unnamed: D574.1 (DOUT), D575.3 (DIN)
unnamed: D575.1 (DOUT), D576.3 (DIN)
unnamed: D576.1 (DOUT), D577.3 (DIN)
unnamed: D577.1 (DOUT), D578.3 (DIN)
unnamed: D578.1 (DOUT), D579.3 (DIN)
unnamed: D579.1 (DOUT), D580.3 (DIN)
unnamed: D580.1 (DOUT), D581.3 (DIN)
unnamed: D581.1 (DOUT), D582.3 (DIN)
unnamed: D582.1 (DOUT), D583.3 (DIN)
unnamed: D583.1 (DOUT), D584.3 (DIN)
unnamed: D584.1 (DOUT), D585.3 (DIN)
unnamed: D585.1 (DOUT), D586.3 (DIN)
unnamed: D586.1 (DOUT), D587.3 (DIN)
unnamed: D587.1 (DOUT), D588.3 (DIN)
unnamed: D588.1 (DOUT), D589.3 (DIN)
unnamed: D589.1 (DOUT), D590.3 (DIN)
unnamed: D590.1 (DOUT), D591.3 (DIN)
unnamed: D591.1 (DOUT), D592.3 (DIN)
unnamed: D592.1 (DOUT), D593.3 (DIN)
unnamed: D593.1 (DOUT), D594.3 (DIN)
unnamed: D594.1 (DOUT), D595.3 (DIN)
unnamed: D595.1 (DOUT), D596.3 (DIN)
unnamed: D596.1 (DOUT), D597.3 (DIN)
unnamed: D597.1 (DOUT), D598.3 (DIN)
unnamed: D598.1 (DOUT), D599.3 (DIN)
unnamed: D599.1 (DOUT), D600.3 (DIN)
unnamed: D601.1 (DOUT), D602.3 (DIN)
unnamed: D602.1 (DOUT), D603.3 (DIN)
unnamed: D603.1 (DOUT), D604.3 (DIN)
unnamed: D604.1 (DOUT), D605.3 (DIN)
unnamed: D605.1 (DOUT), D606.3 (DIN)
unnamed: D606.1 (DOUT), D607.3 (DIN)
unnamed: D607.1 (DOUT), D608.3 (DIN)
unnamed: D608.1 (DOUT), D609.3 (DIN)
unnamed: D609.1 (DOUT), D610.3 (DIN)
unnamed: D610.1 (DOUT), D611.3 (DIN)
unnamed: D611.1 (DOUT), D612.3 (DIN)
unnamed: D612.1 (DOUT), D613.3 (DIN)
unnamed: D613.1 (DOUT), D614.3 (DIN)
unnamed: D614.1 (DOUT), D615.3 (DIN)
unnamed: D615.1 (DOUT), D616.3 (DIN)
unnamed: D616.1 (DOUT), D617.3 (DIN)
unnamed: D617.1 (DOUT), D618.3 (DIN)
unnamed: D618.1 (DOUT), D619.3 (DIN)
unnamed: D619.1 (DOUT), D620.3 (DIN)
unnamed: D620.1 (DOUT), D621.3 (DIN)
unnamed: D621.1 (DOUT), D622.3 (DIN)
unnamed: D622.1 (DOUT), D623.3 (DIN)
unnamed: D623.1 (DOUT), D624.3 (DIN)
unnamed: D624.1 (DOUT), D625.3 (DIN)
unnamed: D625.1 (DOUT), D626.3 (DIN)
unnamed: D626.1 (DOUT), D627.3 (DIN)
unnamed: D627.1 (DOUT), D628.3 (DIN)
unnamed: D628.1 (DOUT), D629.3 (DIN)
unnamed: D629.1 (DOUT), D630.3 (DIN)
unnamed: D630.1 (DOUT), D631.3 (DIN)
unnamed: D631.1 (DOUT), D632.3 (DIN)
unnamed: D632.1 (DOUT), D633.3 (DIN)
unnamed: D633.1 (DOUT), D634.3 (DIN)
unnamed: D634.1 (DOUT), D635.3 (DIN)
unnamed: D635.1 (DOUT), D636.3 (DIN)
unnamed: D636.1 (DOUT), D637.3 (DIN)
unnamed: D637.1 (DOUT), D638.3 (DIN)
unnamed: D638.1 (DOUT), D639.3 (DIN)
unnamed: D639.1 (DOUT), D640.3 (DIN)
unnamed: D640.1 (DOUT), D641.3 (DIN)
unnamed: D641.1 (DOUT), D642.3 (DIN)
unnamed: D642.1 (DOUT), D643.3 (DIN)
unnamed: D643.1 (DOUT), D644.3 (DIN)
unnamed: D644.1 (DOUT), D645.3 (DIN)
unnamed: D645.1 (DOUT), D646.3 (DIN)
unnamed: D646.1 (DOUT), D647.3 (DIN)
unnamed: D647.1 (DOUT), D648.3 (DIN)
unnamed: D648.1 (DOUT), D649.3 (DIN)
unnamed: D649.1 (DOUT), D650.3 (DIN)
unnamed: D650.1 (DOUT), D651.3 (DIN)
unnamed: D651.1 (DOUT), D652.3 (DIN)
unnamed: D652.1 (DOUT), D653.3 (DIN)
unnamed: D653.1 (DOUT), D654.3 (DIN)
unnamed: D654.1 (DOUT), D655.3 (DIN)
unnamed: D655.1 (DOUT), D656.3 (DIN)
unnamed: D656.1 (DOUT), D657.3 (DIN)
unnamed: D657.1 (DOUT), D658.3 (DIN)
unnamed: D658.1 (DOUT), D659.3 (DIN)
unnamed: D659.1 (DOUT), D660.3 (DIN)
unnamed: D660.1 (DOUT), D661.3 (DIN)
unnamed: D661.1 (DOUT), D662.3 (DIN)
unnamed: D662.1 (DOUT), D663.3 (DIN)
unnamed: D663.1 (DOUT), D664.3 (DIN)
unnamed: D664.1 (DOUT), D665.3 (DIN)
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
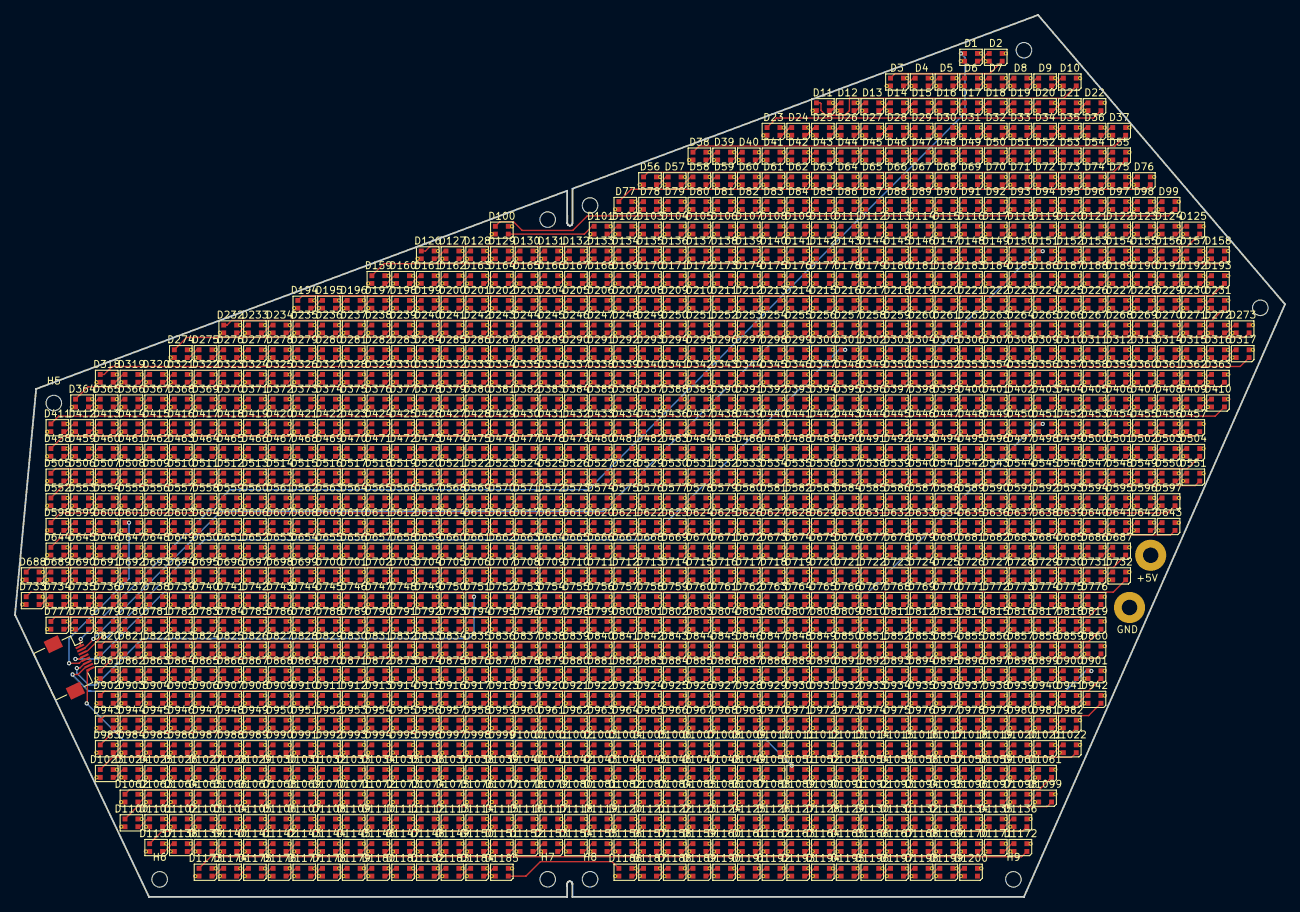
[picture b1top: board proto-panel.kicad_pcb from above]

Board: 4 copper layers, 180.0 x 125.0 mm, 1212 parts (0 on the bottom side), 1202 nets.

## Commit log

2026-03-09 Initial KiCad project generation
2026-03-09 no no what no what what
2026-03-16 Final updates
2026-03-26 Add right side version of PCB
